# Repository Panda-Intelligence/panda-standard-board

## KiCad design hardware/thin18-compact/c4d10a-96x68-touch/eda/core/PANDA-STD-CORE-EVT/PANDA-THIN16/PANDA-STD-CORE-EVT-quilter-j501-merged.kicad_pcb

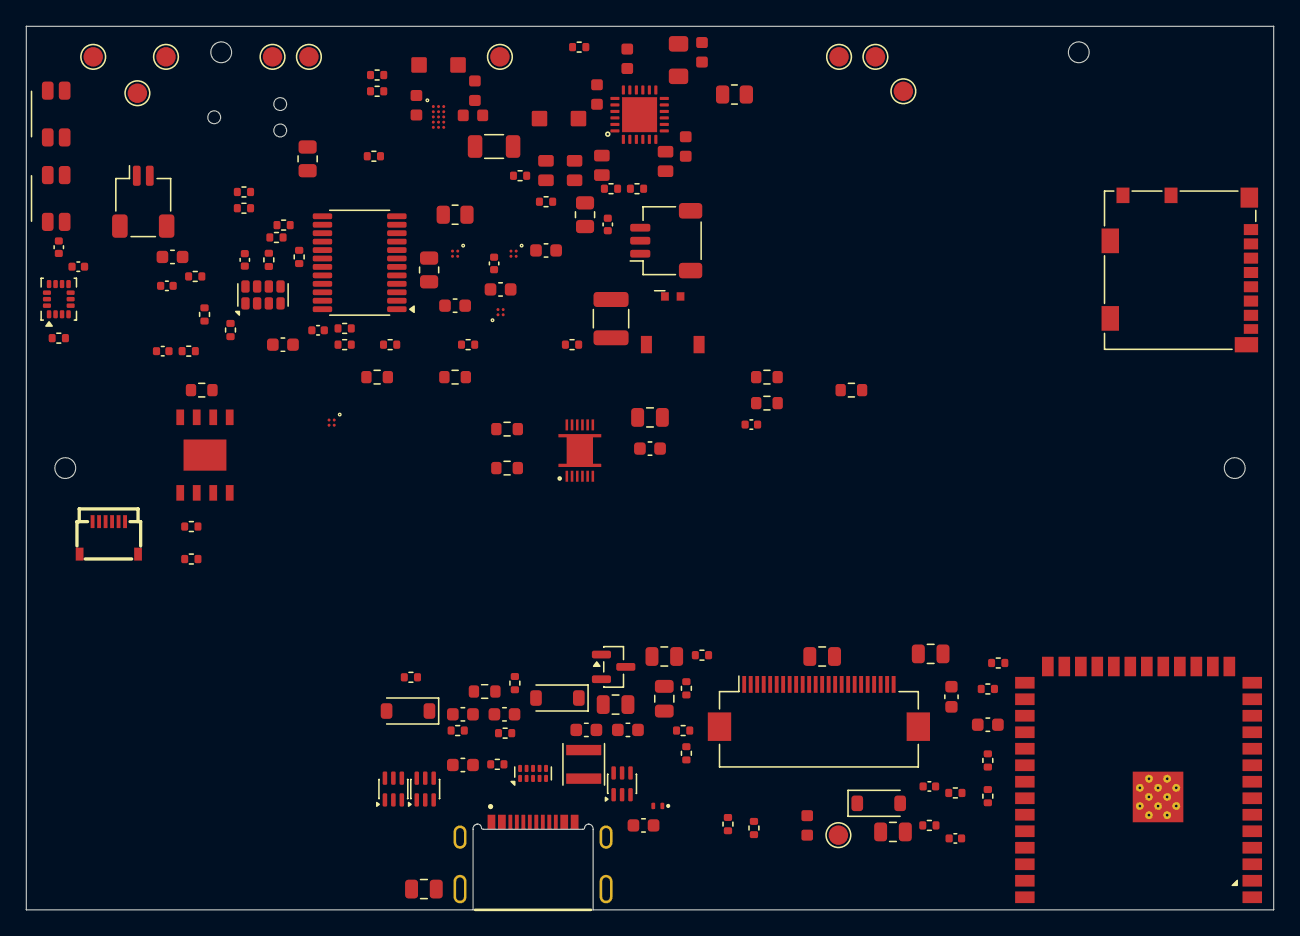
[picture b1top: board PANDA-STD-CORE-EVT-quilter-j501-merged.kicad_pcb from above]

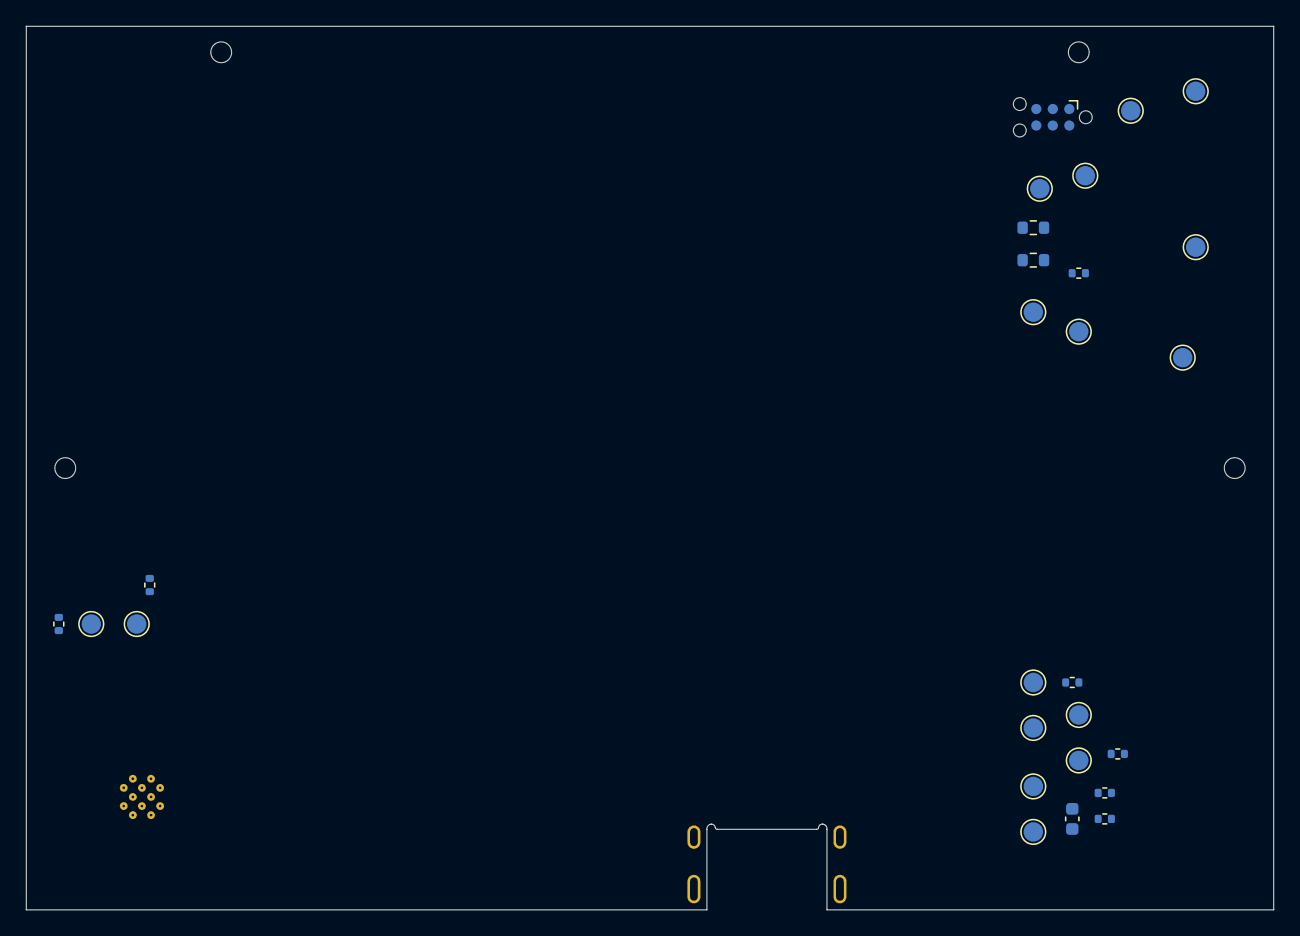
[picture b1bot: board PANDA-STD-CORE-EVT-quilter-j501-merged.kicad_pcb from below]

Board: 4 copper layers, 96.0 x 68.0 mm, 179 parts (27 on the bottom side), 112 nets, no tracks yet.

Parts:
C201: 47n / CBOOT; C201_CBOOT_0603_SEED
C202: 1u / VBUS; C202_CVBUS_0603_ENVELOPE
C203: 10u / PMID; C203_CPMID_1206_ENVELOPE
C204: 330n / ILIM-RC; C204_ILIM_RC_0603_SEED
C205: 4.7u / REGN; C205_CREGN_0805_ENVELOPE
C206: 10u / BAT; C206_CBAT_0805_ENVELOPE
C207: 22u / CSYS1; C207_CSYS_0805_ENVELOPE
C208: 22u / CSYS2; C208_CSYS_0805_ENVELOPE
C209: 1u; C_0603_1608Metric
C301: CPH3225A 11mF 3.3V RTC backup candidate; C_1210_3225Metric
C302: 100n / RTC VDD; C_0402_1005Metric
C303: 1u / BQ BAT; C_0402_1005Metric
C304: 2.2u / BQ VDD; C_0402_1005Metric
C401: 22u / VIN; C_0603_POWER_SEED
C402, C403: 22u / VOUT; C_0603_POWER_SEED
C501: 22u / ESP32; C_0805_2012Metric
C502: 100n / ESP32; C_0402_1005Metric
C503: 100n / VDD_IO; C_0402_1005Metric
C504: 100n / VDD; C_0402_1005Metric
C505: 100n / AUDIO_VDD; C_0402_1005Metric
C506: 10u / AUDIO_VDD; C_0603_1608Metric
C507: 1u / U405 VIN; C_0603_1608Metric
C508: 1u / U402 VIN; C_0603_1608Metric
C509: 1u / U403 VIN; C_0603_1608Metric
C510: 1u / CHIP_PU; C_0603_1608Metric
C511: 1u / U404 VIN; C_0603_1608Metric
C512: 100n / SD VDD; C_0402_1005Metric
C513: 10u / SD VDD; C_0603_1608Metric
C514, C515: DNP / USB tuning; C_0402_1005Metric
C601: 100n / U601 VCC; C_0402_1005Metric
C801, C802, C803: 1u 25V X5R; C_0603_1608Metric
C804, C805, C806, C807, C808, C809: 4.7u 25V X5R; C_0805_2012Metric
C810: 1u 25V X7R; C_0805_2012Metric
C811, C812, C813: 100n 25V X7R; C_0603_1608Metric
C903: 1u / CW2217 VCELL; C_0603_1608Metric
D201: TPD4E05U06DQAR; USON-10_2.5x1.0mm_P0.5mm
D202: TPD1E10B06DPYR; Texas_DPY0002A_0.6x1mm_P0.65mm
D801, D802, D803: MBR0530T1G; D_SOD-123
H801, H802, H803, H804: M1.2 clearance / NPTH 1.6; MountingHole_M1.2_1.6mm
J201: USB4500-03-0-A; USB4500_08mm_MidMount_LayoutReview
J301: DF58-2P-1.2V(21); Hirose_DF58-2P-1.2V_1x02_P1.2mm_Vertical
J302: SM03B-SRSS-TB NTC; JST_SH_SM03B-SRSS-TB_1x03-1MP_P1.00mm_Horizontal
J501: 104031-0811 / microSD; microSD_HC_Molex_104031-0811
J502: SM02B-SRSS-TB; JST_SH_SM02B-SRSS-TB_1x02-1MP_P1.00mm_Horizontal
J503: TC2030-IDC-NL / DEBUG; Tag-Connect_TC2030-IDC-NL_2x03_P1.27mm_Vertical
J802: FH12-24S-0.5SH(55); Hirose_FH12-24S-0.5SH_1x24-1MP_P0.50mm_Horizontal
J803: FH34SRJ-6S-0.5SH(50); FH34SRJ-6S-0.5SH_50
L401: 0.47uH / M0-PENDING; L401_XFL4015_ENVELOPE
L402: 2.2u / BQ buck; L402_2U2_ENVELOPE
L801: 47u 0.25A; L_Taiyo_NRH3010_3030
Q801: NX3008NBK,215; SOT-23
R201: 5.6k / ILIM; R201_ILIM_0603_SEED
R204: 1.2k / ILIM-RC; R204_ILIM_RC_0603_SEED
R206, R207: 5.1k / USB-C Rd; R_0402_1005Metric
R301: 1M / SCL PD DNP; R_0402_1005Metric
R302: 1M / SDA PD DNP; R_0402_1005Metric
R303: 10k / RTC EVI PU; R_0402_1005Metric
R304: 10k / VBACKUP no-backup / DNP with C301; R_0402_1005Metric
R305: 100k / IRQ PU DNP; R_0402_1005Metric
R306: 10m / CW2217 SHUNT; R_1206_3216Metric
R501: 100k / IMU_INT1; R_0402_1005Metric
R502: 100k / EXP_INT_PU; R_0402_1005Metric
R507: 100k / AUDIO_EN_PD; R_0402_1005Metric
R508: 0R / MB6 AUDIO; R_0805_2012Metric
R509: 0R / MB2 3V3_AON; R_0805_2012Metric
R510: 10k / CHIP_PU; R_0402_1005Metric
R511: 10k / GPIO0; R_0402_1005Metric
R512: 10k / GPIO3; R_0402_1005Metric
R513: 10k / GPIO46; R_0402_1005Metric
R514: 0R / MB3 SD; R_0805_2012Metric
R515: 0R / MB4 TOUCH; R_0805_2012Metric
R516: 0R / MB5 EPD; R_0805_2012Metric
R517, R518, R519, R520, R521, R522: 0R / SD series; R_0603_1608Metric
R523, R524, R525, R526, R527: 10k / SD pull-up; R_0402_1005Metric
R528, R814: 10k; R_0402_1005Metric
R529, R530, R801, R802, R803, R804, R805: 22; R_0402_1005Metric
R600: 10k 1% / PG_PU; R_0402_1005Metric
R601: 100k / P15_PD; R_0402_1005Metric
R604: 100k / SD_EN_PD; R_0402_1005Metric
R605: 100k / TOUCH_EN_PD; R_0402_1005Metric
R606: 100k / EPD_EN_PD; R_0402_1005Metric
R607: 100k / BQ_CE_PD; R_0402_1005Metric
R608: 100k / FUEL_PU; R_0402_1005Metric
R609: 100k / BQ_INT_PU; R_0402_1005Metric
R610: 100k / BQ_STAT_PU; R_0402_1005Metric
R611: 100k / KEY_FN_PU; R_0402_1005Metric
R612: 100k / SD_CD_PU; R_0402_1005Metric
R613: 2.2k / I2C_SCL_PU A; R_0402_1005Metric
R614: 2.2k / I2C_SDA_PU A; R_0402_1005Metric
R615: 5.23k; R_0603_1608Metric
R616: 30.1k; R_0603_1608Metric
R806: 100; R_0402_1005Metric
R807, R808, R809, R810, R811, R812: 100k; R_0402_1005Metric
R813: 2.2 1%; R_0603_1608Metric
R903: 100R / CW2217 VDD; R_0603_1608Metric
R904: 100R / CW2217 VCELL; R_0603_1608Metric
R910: 10k / TOUCH_INT_PU; R_0402_1005Metric
R911: 10k / TOUCH_RST_PU; R_0402_1005Metric
SW201, SW202: SKSCLCE010; SW_Alps_SKSCLCE010
TP1: VBUS_USB; TestPoint_Pad_D1.5mm
TP2: VSYS_RAW; TestPoint_Pad_D1.5mm
TP3: 3V3_AON; TestPoint_Pad_D1.5mm
TP4: BAT+; TestPoint_Pad_D1.5mm
TP5: 3V3_SD; TestPoint_Pad_D1.5mm
TP6: 3V3_TOUCH; TestPoint_Pad_D1.5mm
TP7: 3V3_EPD_LOGIC; TestPoint_Pad_D1.5mm
TP8: VSYS_AUDIO; TestPoint_Pad_D1.5mm
TP11: I2C_SCL; TestPoint_Pad_D1.5mm
TP12: I2C_SDA; TestPoint_Pad_D1.5mm
TP13: EXP_INT; TestPoint_Pad_D1.5mm
TP14: EXP_INT / SHARED_IRQ; TestPoint_Pad_D1.5mm
TP16: PG_3V3_MAIN; TestPoint_Pad_D1.5mm
TP18: CHIP_PU; TestPoint_Pad_D1.5mm
TP801: Reserved EPD_D6; TestPoint_Pad_D1.5mm
TP802: Reserved EPD_D7; TestPoint_Pad_D1.5mm
TP803: Reserved EPD_CKH; TestPoint_Pad_D1.5mm
TP804: Reserved EPD_STV; TestPoint_Pad_D1.5mm
TP805: Reserved EPD_CKV; TestPoint_Pad_D1.5mm
TP806: Reserved EPD_STH; TestPoint_Pad_D1.5mm
TPG1, TPG2, TPG3, TPG4, TPG5, TPG6: GND; TestPoint_Pad_D1.5mm
U302: RV-3028-C7; MicroCrystal_C7_SON-8_1.5x3.2mm_P0.9mm
U402, U403, U404, U405: TPS22916CYFPT; TPS22916CYFPT_YFP0004
U501: ESP32-S3-WROOM-1U-N16R8; ESP32-S3-WROOM-1U
U503: QMI8658A; LGA-14_3x2.5mm_P0.5mm_LayoutBorder3x4y
U601: XL9535; TCA9535PWR_PW0024A
U801, U802, U803: AIP74LVC2G17GC363.TR; SOT-363_SC-70-6
U901: SGM41513YTQF24G/TR; SGM41513_YTQF24_4x4_P0.5_EP2.7
U902: SGM62125AXG/TR; SGM62125_XG_WLCSP15_1.46x2.3_P0.4
U903: CW2217BAAD; CW2217BAAD_DFN12_L4.0_W2.5_P0.4_EP
U904: NS4168; NS4168_ESOP8_EP_L4.9_W3.9_P1.27

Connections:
3V3_AON: C302.1, C501.1, C502.1, C503.1, C504.1, C508.1, C509.1, C511.1, C601.1, J503.2, R303.1, R305.1, R502.2, R509.2, R510.1, R511.1, R528.1, R600.2, R608.2, R609.2, R610.2, R611.2, R612.2, R613.2, R614.2, TP3.1, U302.7, U402.A2, U403.A2, U404.A2, U501.2, U503.1, U503.5, U503.8, U503.12, U601.24, U901.2
3V3_AON_SRC: C402.1, C403.1, R509.1, U902.E2, U902.E3
3V3_EPD_LOGIC: C801.1, C802.1, C811.1, C812.1, C813.1, J802.15, J802.16, L801.1, R516.2, R809.2, TP7.1, U801.5 (VCC), U802.5 (VCC), U803.5 (VCC)
3V3_EPD_LOGIC_SW: R516.1, U404.A1
3V3_SD: C512.1, C513.1, J501.4, R514.2, R523.2, R524.2, R525.2, R526.2, R527.2, TP5.1
3V3_SD_SW: R514.1, U402.A1
3V3_TOUCH: J803.2, R515.2, R910.1, R911.1, TP6.1
3V3_TOUCH_SW: R515.1, U403.A1
BAT_CONN_P: J301.1, R306.1, R904.1, TP4.1, U903.8
BAT_PACKP: C206.1, C303.1, R306.2, R903.1, U901.13, U901.14, U903.7
BQ_CE: R607.1, U601.9, U901.9
BQ_ILIM: R201.1, R204.1
BQ_ILIM_RC: C204.1, R204.2
BQ_INT: R609.1, U601.10, U901.7
BQ_PG: R600.1, U601.13, U901.3
BQ_QON: SW202.1, U901.12
BQ_STAT: R610.1, U601.11, U901.4
BQ_TS: J302.1, R615.2, R616.1, U901.11, U903.9
CHIP_PU: C510.1, J503.1, R510.2, TP18.1, U501.3
EN_3V3_EPD_LOGIC: R606.1, U404.B2, U601.6
EN_3V3_SD: R604.1, U402.B2, U601.4
EN_3V3_TOUCH: R605.1, U403.B2, U601.5
EN_VSYS_AUDIO: R507.1, U405.B2, U601.7
EPD16_BOOST_CP: C804.2, D801.1 (K), D802.2 (A)
EPD16_BOOST_SW: C804.1, D803.2 (A), L801.2, Q801.3 (D)
EPD16_BUF_CS: R803.1, U802.6 (1Y)
EPD16_BUF_DC: R804.1, U802.4 (2Y)
EPD16_BUF_MOSI: R802.1, U801.4 (2Y)
EPD16_BUF_RESET: R805.1, U803.6 (1Y)
EPD16_BUF_SCLK: R801.1, U801.6 (1Y)
EPD16_BUSY: J802.9, R806.1
EPD16_CS: J802.12, R803.2
EPD16_DC: J802.11, R804.2
EPD16_GDR: J802.2, Q801.1 (G), R814.1
EPD16_MOSI: J802.14, R802.2
EPD16_RESE: J802.3, Q801.2 (S), R813.1
EPD16_RESET: J802.10, R805.2
EPD16_SCLK: J802.13, R801.2
EPD16_VCOM: C810.1, J802.24
EPD16_VDD1V5: C803.1, J802.18
EPD16_VGH: C806.1, D803.1 (K), J802.21
EPD16_VGL: C805.1, D801.2 (A), J802.23
EPD16_VSH1: C808.1, J802.20
EPD16_VSH2: C807.1, J802.5
EPD16_VSL: C809.1, J802.22
EPD_CKH: TP803.1, U501.9
EPD_CKV: TP805.1, U501.11
EPD_D0: R807.1, U501.31, U801.1 (1A)
EPD_D1: R808.1, U501.32, U801.3 (2A)
EPD_D2: R809.1, U501.33, U802.1 (1A)
EPD_D3: R810.1, U501.34, U802.3 (2A)
EPD_D4: R811.1, U501.35, U803.1 (1A)
EPD_D5: R806.2, R812.1, U501.24
EPD_D6: TP801.1, U501.25
EPD_D7: TP802.1, U501.23
EPD_LE: R512.1, U501.15
EPD_OE: R513.1, U501.16
EPD_STH: TP806.1, U501.26
EPD_STV: TP804.1, U501.10
EXP_INT: R305.2, R502.1, TP13.1, TP14.1, U302.2, U501.4, U601.1
EXP_P15_SPARE: R601.1, U601.18
FUEL_GPOUT: R608.1, U601.8, U903.1
FUEL_VCELL: C903.1, R904.2, U903.4
FUEL_VDD: C304.1, R903.2, U903.3
GND: C202.2, C203.2, C204.2, C205.2, C206.2, C207.2, C208.2, C209.2, C301.2, C302.2, C303.2, C304.2, C401.2, C402.2, C403.2, C501.2, C502.2, C503.2, C504.2, C505.2, C506.2, C507.2, C508.2, C509.2, C510.2, C511.2, C512.2, C513.2, C514.2, C515.2, C601.2, C801.2, C802.2, C803.2, C805.2, C806.2, C807.2, C808.2, C809.2, C810.2, C811.2, C812.2, C813.2, C903.2, D201.3, D201.8, D202.2, D802.1 (K), J201.A1, J201.A12, J201.B1, J201.B12, J201.SH, J301.2, J302.2, J501.6, J501.10, J501.SH, J503.4, J802.8, J802.17, J803.1, R201.2, R206.1, R207.1, R301.2, R302.2, R304.2, R501.2, R507.2, R512.2, R513.2, R601.2, R604.2, R605.2, R606.2, R607.2, R616.2, R807.2, R808.2, R810.2, R811.2, R812.2, R813.2, R814.2, SW201.2, SW202.2, TPG1.1, TPG2.1, TPG3.1, TPG4.1, TPG5.1, TPG6.1, U302.5, U402.B1, U403.B1, U404.B1, U405.B1, U501.1, U501.40, U501.41, U503.2, U503.3, U503.6, U503.7, U601.2, U601.3, U601.12, U601.21, U801.2 (GND), U802.2 (GND), U803.2 (GND), U803.3 (2A), U901.17, U901.18, U901.25, U902.C1, U902.C2, U902.C3, U903.6, U903.13, U904.7, U904.9
GPIO0: J503.6, R511.2, U501.27
I2C_SCL: J803.6, R301.1, R613.1, TP11.1, U302.3, U501.22, U503.13, U601.22, U901.5, U902.D1, U903.11
I2C_SDA: J803.5, R302.1, R614.1, TP12.1, U302.4, U501.8, U503.14, U601.23, U901.6, U902.E1, U903.10
I2S_BCLK: U501.19, U904.3
I2S_DIN: U501.21, U904.4
I2S_LRCLK: U501.20, U904.2
IMU_INT1: R501.1, U503.4, U601.15
KEY_FN: R611.1, U601.14
KEY_POWER_MCU: R528.2, SW201.1, U501.39
PG_3V3_MAIN: TP16.1, U601.17
RTC_EVI: R303.2, U302.8
RTC_VBACKUP: C301.1, R304.1, U302.6
SDMMC_CLK: R517.1, U501.5
SDMMC_CLK_CARD: J501.5, R517.2
SDMMC_CMD: R518.1, U501.6
SDMMC_CMD_CARD: J501.3, R518.2, R523.1
SDMMC_D0: R519.1, U501.7
SDMMC_D0_CARD: J501.7, R519.2, R524.1
SDMMC_D1: R520.1, U501.12
SDMMC_D1_CARD: J501.8, R520.2, R525.1
SDMMC_D2: R521.1, U501.17
SDMMC_D2_CARD: J501.1, R521.2, R526.1
SDMMC_D3: R522.1, U501.18
SDMMC_D3_CARD: J501.2, R522.2, R527.1
SD_CD: J501.9, R612.1, U601.16
SGM41513_BTST: C201.1, U901.21
SGM41513_PMID: C203.1, U901.23
SGM41513_REGN: C205.1, R615.1, U901.22
SGM41513_SW: C201.2, L402.1, U901.19, U901.20
SGM62125_SW1: L401.1, U902.B2, U902.B3
SGM62125_SW2: L401.2, U902.D2, U902.D3
SPK_N: J502.2, U904.5
SPK_P: J502.1, U904.8
TOUCH_INT: J803.4, R910.2, U601.19
TOUCH_RST: J803.3, R911.2, U601.20
UART0_RX: J503.3, U501.36
UART0_TX: J503.5, U501.37
USB_CC1: D201.4, J201.A5, R206.2
USB_CC2: D201.5, J201.B5, R207.2
USB_DM: D201.2, J201.A7, J201.B7, R530.1
USB_DM_MCU: C515.1, R530.2, U501.13
USB_DP: D201.1, J201.A6, J201.B6, R529.1
USB_DP_MCU: C514.1, R529.2, U501.14
VBUS_USB: C202.1, C209.1, D202.1, J201.A4, J201.A9, J201.B4, J201.B9, TP1.1, U901.1, U901.24
VSYS_AUDIO: C505.1, C506.1, R508.2, TP8.1, U904.1, U904.6
VSYS_AUDIO_SW: R508.1, U405.A1
VSYS_RAW: C207.1, C208.1, C401.1, C507.1, L402.2, TP2.1, U405.A2, U901.15, U901.16, U902.A1, U902.A2, U902.A3, U902.B1

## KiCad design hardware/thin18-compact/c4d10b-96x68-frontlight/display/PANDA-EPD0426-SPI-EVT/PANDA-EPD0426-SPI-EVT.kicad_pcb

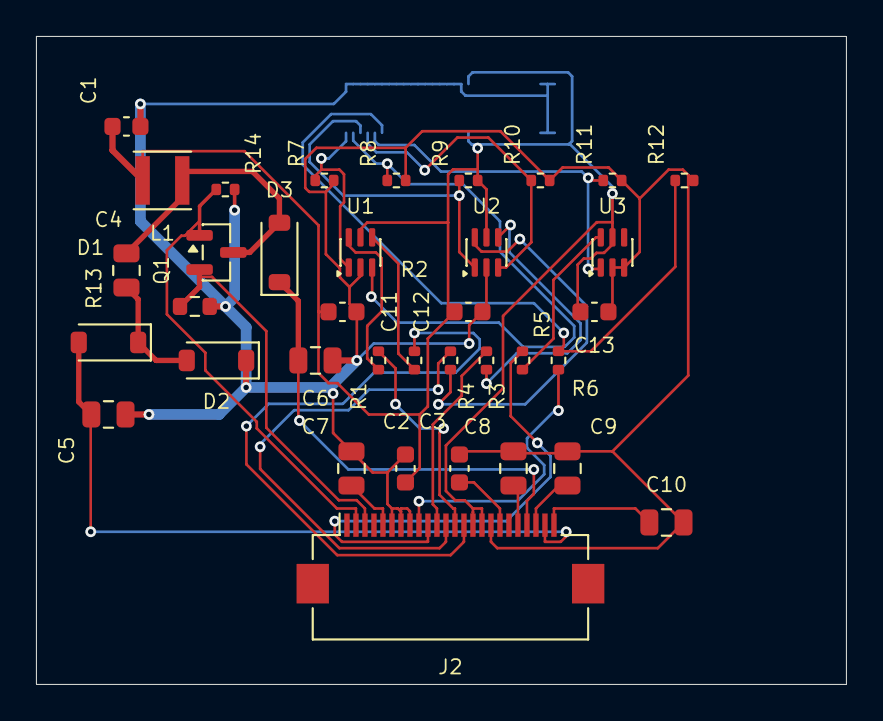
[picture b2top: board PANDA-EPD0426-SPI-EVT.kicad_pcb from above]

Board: 2 copper layers, 45.0 x 36.0 mm, 37 parts (1 on the bottom side), 30 nets.

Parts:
C1, C2, C3: 1u 25V X5R; C_0603_1608Metric
C4, C5, C6, C7, C8, C9: 4.7u 25V X5R; C_0805_2012Metric
C10: 1u 25V X7R; C_0805_2012Metric
C11, C12, C13: 100n 25V X7R; C_0603_1608Metric
D1, D2, D3: MBR0530T1G; D_SOD-123
J1: DF40C-60DP-0.4V(51); Hirose_DF40C-60DP-0.4V_2x30-1MP_P0.4mm
J2: FH12-24S-0.5SH(55); Hirose_FH12-24S-0.5SH_1x24-1MP_P0.50mm_Horizontal
L1: 47u 0.25A; L_Taiyo_NRH3010_3030
Q1: NX3008NBK,215; SOT-23
R1, R2, R3, R4, R5: 22; R_0402_1005Metric
R6: 100; R_0402_1005Metric
R7, R8, R9, R10, R11, R12: 100k; R_0402_1005Metric
R13: 2.2 1%; R_0603_1608Metric
R14: 10k; R_0402_1005Metric
U1, U2, U3: SN74AUP2G17DCKR; SOT-363_SC-70-6

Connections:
/BOOST_CP: C4.2, D1.1 (K), D2.2 (A)
/BOOST_SW: C4.1, D3.2 (A), L1.2, Q1.3 (D)
/BUF_CS: R3.1, U2.6 (1Y)
/BUF_DC: R4.1, U2.4 (2Y)
/BUF_MOSI: R2.1, U1.4 (2Y)
/BUF_RESET: R5.1, U3.6 (1Y)
/BUF_SCLK: R1.1, U1.6 (1Y)
/BUSY: J2.9, R6.1
/CS: J2.12, R3.2
/DC: J2.11, R4.2
/EPD_3V3: C1.1, C2.1, C11.1, C12.1, C13.1, J1.35, J1.36, J2.15, J2.16, L1.1, R9.2, U1.5 (VCC), U2.5 (VCC), U3.5 (VCC)
/GDR: J2.2, Q1.1 (G), R14.1
/GND: C1.2, C2.2, C3.2, C5.2, C6.2, C7.2, C8.2, C9.2, C10.2, C11.2, C12.2, C13.2, D2.1 (K), J1.2, J1.4, J1.6, J1.8, J1.10, J1.12, J1.14, J1.16, J1.18, J1.20, J1.22, J1.24, J1.26, J1.28, J1.30, J1.32, J1.34, J1.55, J1.56, J1.57, J1.58, J1.59, J1.60, J2.6, J2.7, J2.8, J2.17, R7.2, R8.2, R10.2, R11.2, R12.2, R13.2, R14.2, U1.2 (GND), U2.2 (GND), U3.2 (GND), U3.3 (2A)
/HOST_BUSY: J1.11, R6.2, R12.1
/HOST_CS: J1.5, R9.1, U2.1 (1A)
/HOST_DC: J1.7, R10.1, U2.3 (2A)
/HOST_MOSI: J1.3, R8.1, U1.3 (2A)
/HOST_RESET: J1.9, R11.1, U3.1 (1A)
/HOST_SCLK: J1.1, R7.1, U1.1 (1A)
/MOSI: J2.14, R2.2
/RESE: J2.3, Q1.2 (S), R13.1
/RESET: J2.10, R5.2
/SCLK: J2.13, R1.2
/VCOM: C10.1, J2.24
/VDD1V5: C3.1, J2.18
/VGH: C6.1, D3.1 (K), J2.21
/VGL: C5.1, D1.2 (A), J2.23
/VSH1: C8.1, J2.20
/VSH2: C7.1, J2.5
/VSL: C9.1, J2.22
